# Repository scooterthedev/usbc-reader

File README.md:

# Powdy

Powdy is an all-in-one power reader via USB-C! Just plug it in to your device, and watch as the power draw reading come onto the OLED screen. This device mostly uses one main component to read the power- The INA226, along with the MCU- the ATmega328P-A.

## Software 
The whole software is being written in Arduino (yes, I know....), and being flashed to the MCU via a USBtinyISP as a HEX file via SPI, and the 6 pin headers on-board.

## BOM
| Item Name        | Purpose in Project                        | Source                   | Item Price (incl. shipping + taxes) | Total Price |
|------------------|--------------------------------------------|---------------------------|--------------------------------------|-------------|
| USB-C   | What connects to the device to read the power output             | JLC - C165948          | $0.84                               | $0.84      |
| OLED| For displaying the reading           | Amazon                   | $7.93                               | $7.93      |
| Caps and Resistors x 14| For everything             | JLC         | $0.29                               | $0.29      |
| 2x03 Pin Header| For programming | Digikey - 61300411121                 | $0.34                                | $0.34       |
| INA226 | the actual IC to measure the power going through the USB-C port                     | JLC - C2653835                 | $9.3                                | $9.3       |
| AMS1117-3.3 | Voltage regulator to 3.3V from 5V for stuff like OLED and some INA226 pins                    | JLC - C6186                   | $0.89                                | $0.89       |
| ATmega328P-A | The Main MCU                     | JLC - C14877                     | $11                                | $11       |
| Crystal | For the MCU | Digi - ABM3-16.000MHZ-B2-T                 | $0.9                               | $0.9      |
| USBtinyISP| The board to program the MCU via the 6 header pins | Amazon                 | $1                               | $11      |
**Total**        - **$43 Before Tax In Parts**
**Total** - **$117 After Everything including assembly + pcb + tax and shipping**

## Photos

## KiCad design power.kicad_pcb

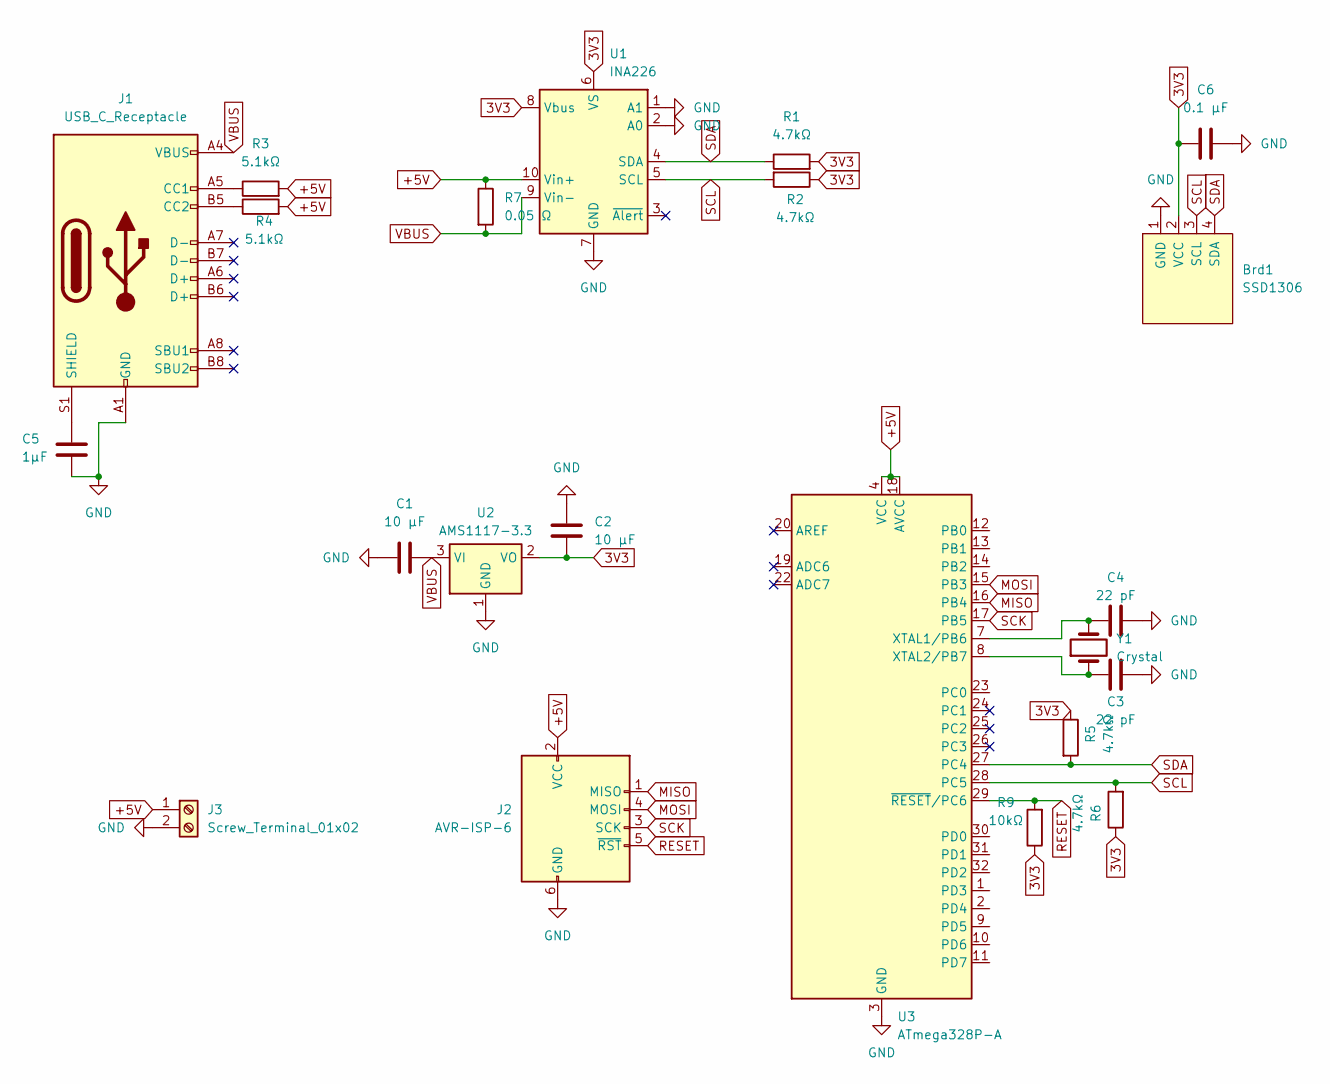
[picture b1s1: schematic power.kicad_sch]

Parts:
Brd1: SSD1306; Adafruit_SSD1306
C1, C2: 10 µF; C_0603_1608Metric
C3, C4: 22 pF; C_0603_1608Metric
C5: 1µF; C_0603_1608Metric
C6: 0.1 µF; C_0603_1608Metric
J1: USB_C_Receptacle; USB_C_Receptacle_Amphenol_124019772112A
J2: AVR-ISP-6; Tag-Connect_TC2030-IDC-NL_2x03_P1.27mm_Vertical
J3: Screw_Terminal_01x02; TerminalBlock_4Ucon_1x02_P3.50mm_Horizontal
R1, R2, R5, R6: 4.7kΩ; R_0603_1608Metric
R3, R4: 5.1kΩ; R_0603_1608Metric
R7: 0.05 Ω; R_0603_1608Metric
R9: 10kΩ; R_0603_1608Metric
U1: INA226; VSSOP-10_3x3mm_P0.5mm
U2: AMS1117-3.3; SOT-223-3_TabPin2
U3: ATmega328P-A; TQFP-32_7x7mm_P0.8mm
Y1: Crystal; Crystal_SMD_0603-2Pin_6.0x3.5mm

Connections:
3V3: Brd1.2 (VCC), C2.1, C6.1, R1.2, R2.1, R5.1, R6.1, R9.1, U1.6 (VS), U1.8 (Vbus), U2.2 (VO)
+5V: J2.2 (VCC), J3.1, R3.2, R4.2, R7.1, U1.10 (Vin+), U3.4 (VCC), U3.6 (VCC), U3.18 (AVCC)
GND: Brd1.1 (GND), C1.1, C2.2, C3.2, C4.2, C5.2, C6.2, J1.A1 (GND), J1.A12 (GND), J1.B1 (GND), J1.B12 (GND), J2.6 (GND), J3.2, U1.1 (A1), U1.2 (A0), U1.7 (GND), U2.1 (GND), U3.3 (GND), U3.5 (GND), U3.21 (GND)
MISO: J2.1 (MISO), U3.16 (PB4)
MOSI: J2.4 (MOSI), U3.15 (PB3)
unnamed: J1.A5 (CC1), R3.1
unnamed: J1.B5 (CC2), R4.1
unnamed: C5.1, J1.S1 (SHIELD)
unnamed: C4.1, U3.7 (XTAL1/PB6), Y1.2
unnamed: C3.1, U3.8 (XTAL2/PB7), Y1.1
RESET: J2.5 (~RST), R9.2, U3.29 (~RESET/PC6)
SCK: J2.3 (SCK), U3.17 (PB5)
SCL: Brd1.3 (SCL), R2.2, R6.2, U1.5 (SCL), U3.28 (PC5)
SDA: Brd1.4 (SDA), R1.1, R5.2, U1.4 (SDA), U3.27 (PC4)
VBUS: C1.2, J1.A4 (VBUS), J1.A9 (VBUS), J1.B4 (VBUS), J1.B9 (VBUS), R7.2, U1.9 (Vin-), U2.3 (VI)

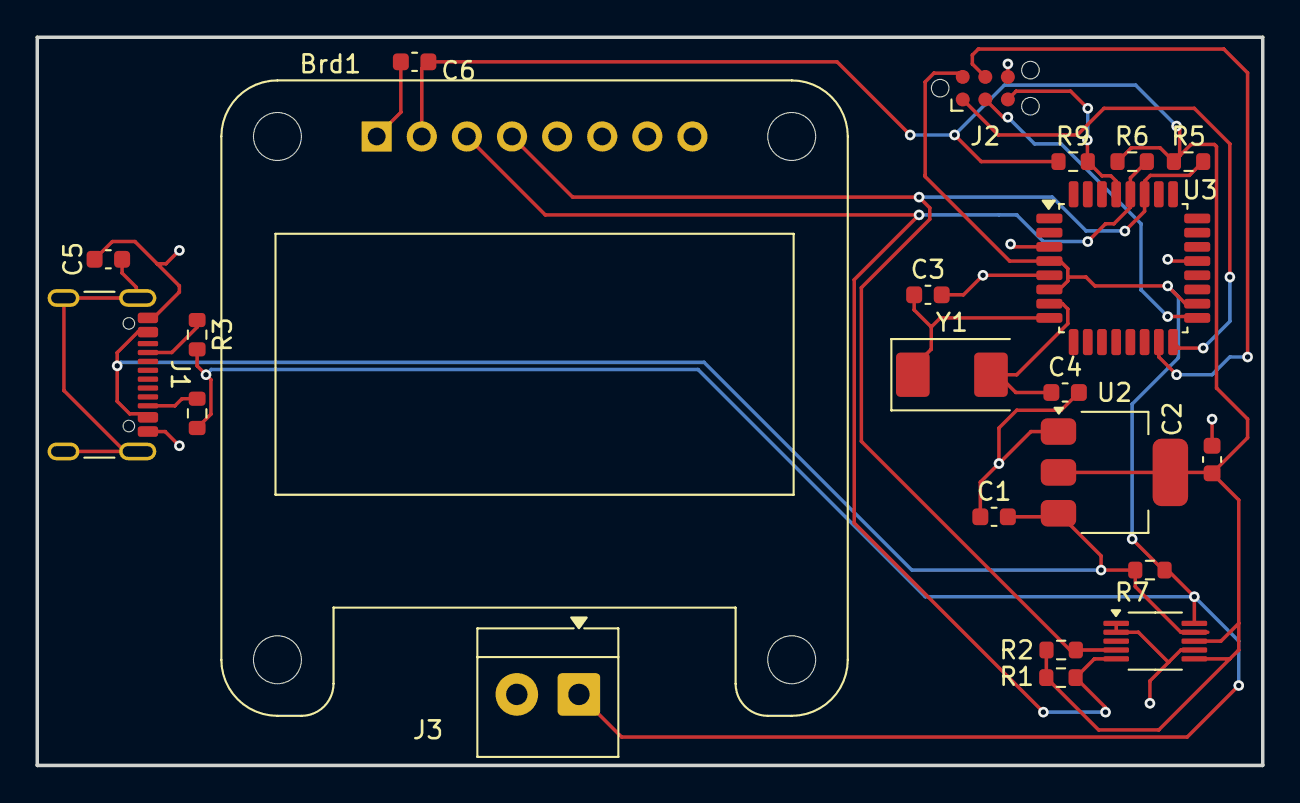
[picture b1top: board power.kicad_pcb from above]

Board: 2 copper layers, 69.0 x 41.0 mm, 22 parts (0 on the bottom side), 15 nets.

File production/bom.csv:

Designator,Footprint,Quantity,Value,LCSC Part #
BRD1,Adafruit_SSD1306,1,SSD1306,
"C1, C2",0603,2,10 µF,
"C3, C4",0603,2,22 pF,
C5,0603,1,1µF,
C6,0603,1,0.1 µF,
J1,USB_C_Receptacle_GCT_USB4105-xx-A_16P_TopMnt_Horizontal,1,USB_C_Receptacle,
J2,Tag-Connect_TC2030-IDC-NL_2x03_P1.27mm_Vertical,1,AVR-ISP-6,
J3,TerminalBlock_4Ucon_1x02_P3.50mm_Horizontal,1,Screw_Terminal_01x02,
"R1, R2, R5, R6",0603,4,4.7kΩ,
"R3, R4",0603,2,5.1kΩ,
R7,0603,1,0.05 Ω,
R9,0603,1,10kΩ,
U1,VSSOP-10_3x3mm_P0.5mm,1,INA226,
U2,SOT-223-3_TabPin2,1,AMS1117-3.3,
U3,TQFP-32_7x7mm_P0.8mm,1,ATmega328P-A,
Y1,Crystal_SMD_0603-2Pin_6.0x3.5mm,1,Crystal,

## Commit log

2025-05-25 Initial parts
2025-05-25 Getting there
2025-05-25 Added custom OLED, finished small changes to the schematic, and started the PCB
2025-05-25 PCB Routing Starting
2025-05-25 Schematic 95% done
2025-05-25 Small DRC Fixes
2025-05-25 Switched to 5V over 3.3V for MCU for programming
2025-05-25 Small PCB changes
2025-05-26 Finished it all!
2025-05-26 Started to write Journal up!
2025-05-26 Finished my Journal
2025-05-26 Added README
2025-05-26 Added photos
2025-05-26 Hopefully software works...
2025-05-26 Added software section
2025-05-27 Finalizing Journal for today
2025-05-28 Possibly fixed it
2025-05-28 Got the corruption gone via a backup!!
2025-05-28 Fixed the few small changes from my revert
2025-06-04 Final fixes
2025-06-05 Switched USB C out to the proper one
